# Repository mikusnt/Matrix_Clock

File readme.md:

# Matrix Clock
Documentation of electronic clock which matrix of LED's controlling by microcontroller ATmega 328P. Communication between clock and user realized by bluetooth. Room brightness determines matrix brightness.
# Processor
ATmega 328P 20MHz  
Period: 0,05 us = 50 ns  
Connected to:
* five shift registers to control the matrix (four to control X axes, one to control Y axis) 
* relay to generate acustic signals (quaters and full hours)
* DS3231 timer by I2C
* HC-06 bluetooth module by RS232
* photoresistor to brightness measurement

# Timers Math calculations

## Main timer (matrix refresh)
8bit Timer0  
Mode: CTC  
Refresh freq: 100 Hz  
Y levels of matrix: 8  
Number of brightness level: 20  
uC period of overflow: 20 000 000 / 100 / 8 / 20 =  1250  
Prescaler: 8  
OCR: 156  

## Logic PWM Timer (PWM matrix brightness)
16bit Timer1
Mode: CTC  
Refresh freq: 100 Hz  
Y levels of matrix: 8  
Number of brightness level: 20  
Number of PWM brightness levels: 3  
uC period of overflow: 20 000 000 / 100 / 8 / 20 / 3 =  417  
Prescaler: 8  
OCR: 52  

## Internal time timer (between DS3231 1Hz overflows)
8bit Timer2  
Mode: CTC  
Freq: 1kHz  
Period: 1ms  
uC period to overflow: 20 000 000 / 1 000 = 20 000  
Prescaler: 256    
OCR: 78  

## Power consumption
Basic mode: 20mA  
High brightness: 66mA  

Basic Mode + Bluetooth: 41mA  
High brightness + Bluetooth: 82mA

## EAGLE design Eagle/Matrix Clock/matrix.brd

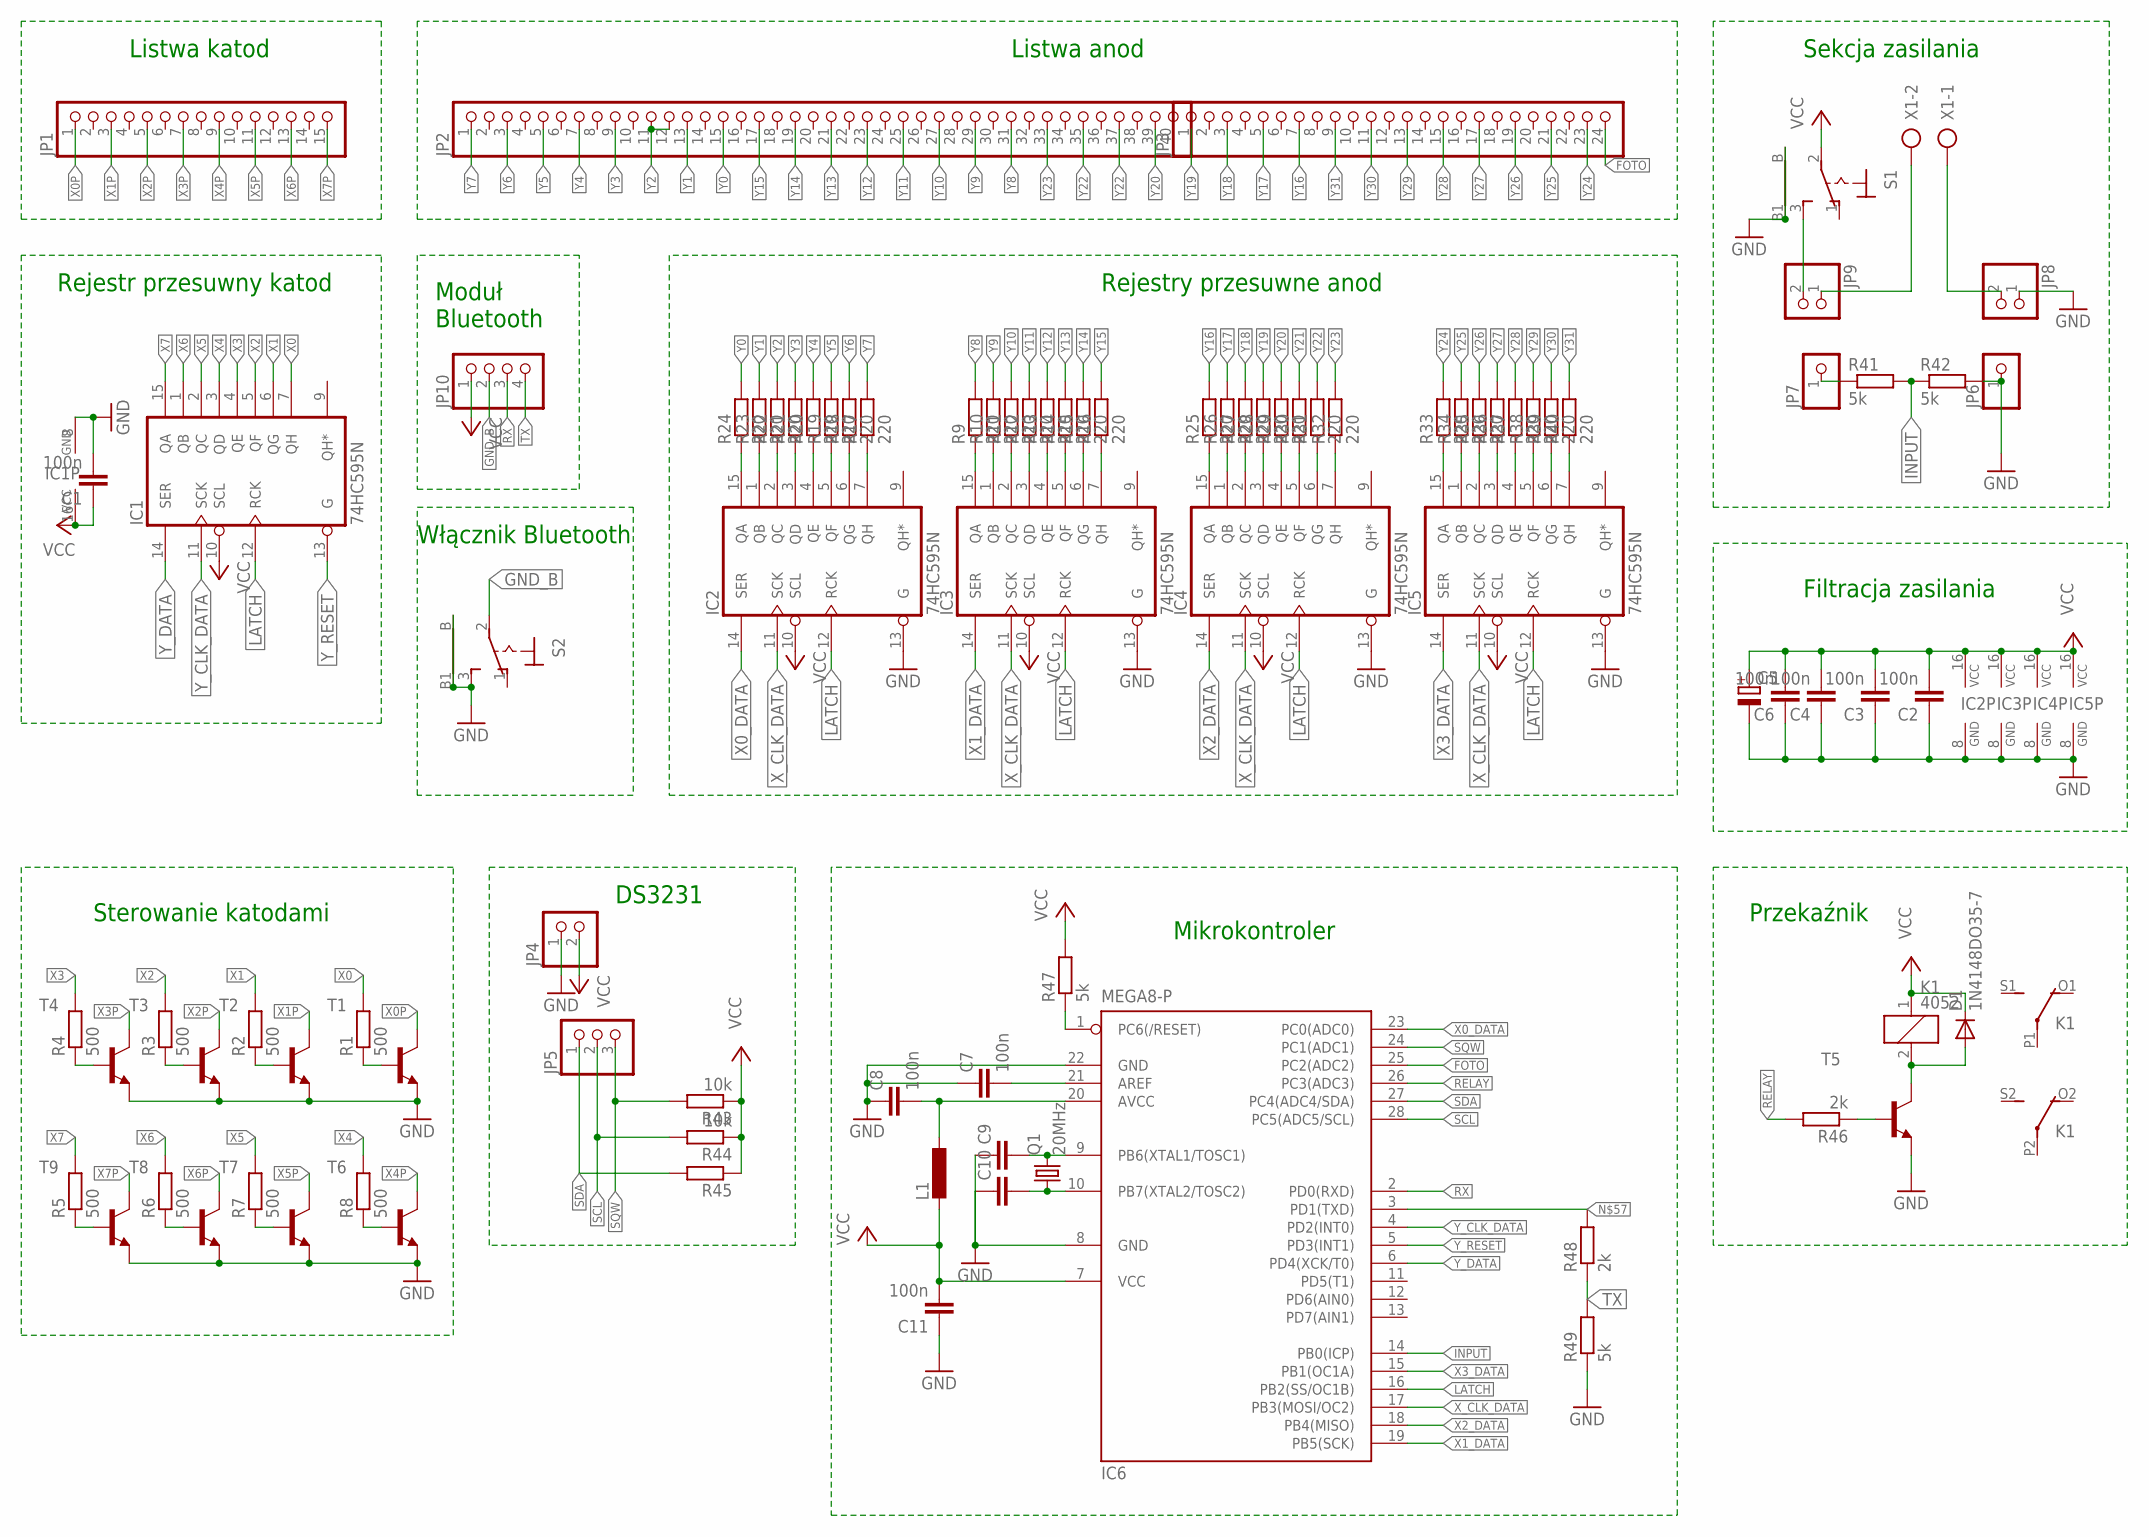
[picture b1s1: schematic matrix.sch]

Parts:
C1, C2, C3, C4, C6, C7, C8, C11: 100n; C025-025X050
C5: CPOL-EUE2.5-7; E2,5-7
C9, C10: C-EU025-025X050; C025-025X050
D1: 1N4148DO35-7; DO35-7
IC1, IC2, IC3, IC4, IC5: 74HC595N; DIL16
IC6: MEGA8-P; DIL28-3
JP1: PINHD-1X15; 1X15
JP2: PINHD-1X40; 1X40
JP3: PINHD-1X24; 1X24
JP4, JP8, JP9: PINHD-1X2; 1X02
JP5: PINHD-1X3; 1X03
JP6, JP7: PINHD-1X1; 1X01
JP10: PINHD-1X4; 1X04
K1: 4052; F4052
L1: L-EU0207/10; 0207/10
Q1: 20MHz; HC49/S
R1, R2, R3, R4, R5, R6, R7, R8: 500; 0204/5
R9, R10, R11, R12, R13, R14, R15, R16, R17, R20, R22, R23, R24, R25, R26, R27, R28, R29, R31, R32, R33, R34, R35, R37, R38, R39, R40: 220; 0204/5
R18, R19: 220; 0204V
R21, R30, R36, R45: R-EU_0204/5; 0204/5
R41, R42, R49: 5k; 0204/5
R43: 10k; 0207/7
R44: 10k; 0204/5
R46: 2k; 0207/7
R47: 5k; 0204V
R48: 2k; 0204/5
S1, S2: 9070-1W
T1, T2, T3, T4, T5, T6, T7, T8, T9: BC337-16-NPN-TO92-CBE; TO92-CBE
X1: AK300/2

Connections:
FOTO: IC6.25 (PC2(ADC2)), JP3.24
GND: C1.2, C2.1, C3.1, C4.1, C5.-, C6.1, C7.1, C8.1, C9.1, C10.1, C11.1, IC1.8 (GND), IC2.8 (GND), IC2.13 (G), IC3.8 (GND), IC3.13 (G), IC4.8 (GND), IC4.13 (G), IC5.8 (GND), IC5.13 (G), IC6.8 (GND), IC6.22 (GND), JP4.1, JP6.1, JP8.1, R42.2, R49.1, S1.B, S1.B1, S2.3 (S), S2.B, S2.B1, T1.E, T2.E, T3.E, T4.E, T5.E, T6.E, T7.E, T8.E, T9.E
GND_B: JP10.2, S2.2
INPUT: IC6.14 (PB0(ICP)), R41.2, R42.1
LATCH: IC1.12 (RCK), IC2.12 (RCK), IC3.12 (RCK), IC4.12 (RCK), IC5.12 (RCK), IC6.16 (PB2(SS/OC1B))
unnamed: R4.1, T4.B
unnamed: JP9.1, X1.2
unnamed: IC2.15 (QA), R24.1
unnamed: R3.1, T3.B
unnamed: R2.1, T2.B
unnamed: R1.1, T1.B
unnamed: R8.1, T6.B
unnamed: R7.1, T7.B
unnamed: R6.1, T8.B
unnamed: R5.1, T9.B
unnamed: JP8.2, X1.1
unnamed: IC2.1 (QB), R23.1
unnamed: IC2.2 (QC), R22.1
unnamed: JP7.1, R41.1
unnamed: IC2.3 (QD), R21.1
unnamed: IC2.4 (QE), R20.1
unnamed: IC2.5 (QF), R19.1
unnamed: IC2.6 (QG), R18.1
unnamed: IC2.7 (QH), R17.1
unnamed: IC3.15 (QA), R9.1
unnamed: IC3.1 (QB), R10.1
unnamed: IC3.2 (QC), R11.1
unnamed: IC3.3 (QD), R12.1
unnamed: IC3.4 (QE), R13.1
unnamed: IC3.5 (QF), R14.1
unnamed: IC3.6 (QG), R15.1
unnamed: IC3.7 (QH), R16.1
unnamed: IC4.7 (QH), R32.1
unnamed: IC4.6 (QG), R31.1
unnamed: IC4.5 (QF), R30.1
unnamed: IC4.4 (QE), R29.1
unnamed: IC4.3 (QD), R28.1
unnamed: IC4.2 (QC), R27.1
unnamed: IC4.1 (QB), R26.1
unnamed: IC4.15 (QA), R25.1
unnamed: JP9.2, S1.3 (S)
unnamed: C9.2, IC6.9 (PB6(XTAL1/TOSC1)), Q1.2
unnamed: C10.2, IC6.10 (PB7(XTAL2/TOSC2)), Q1.1
unnamed: C7.2, IC6.21 (AREF)
unnamed: IC5.15 (QA), R33.1
unnamed: IC5.1 (QB), R34.1
unnamed: IC5.2 (QC), R35.1
unnamed: IC5.3 (QD), R36.1
unnamed: IC5.4 (QE), R37.1
unnamed: IC5.5 (QF), R38.1
unnamed: IC5.6 (QG), R39.1
unnamed: IC5.7 (QH), R40.1
unnamed: C8.2, IC6.20 (AVCC), L1.1
unnamed: D1.A, K1.2, T5.C
unnamed: R46.1, T5.B
unnamed: IC6.1 (PC6(/RESET)), R47.1
unnamed: IC6.3 (PD1(TXD)), R48.2
RELAY: IC6.26 (PC3(ADC3)), R46.2
RX: IC6.2 (PD0(RXD)), JP10.3
SCL: IC6.28 (PC5(ADC5/SCL)), JP5.2, R44.2
SDA: IC6.27 (PC4(ADC4/SDA)), JP5.1, R45.2
SQW: IC6.24 (PC1(ADC1)), JP5.3, R43.2
TX: JP10.4, R48.1, R49.2
VCC: C1.1, C2.2, C3.2, C4.2, C5.+, C6.2, C11.2, D1.C, IC1.10 (SCL), IC1.16 (VCC), IC2.10 (SCL), IC2.16 (VCC), IC3.10 (SCL), IC3.16 (VCC), IC4.10 (SCL), IC4.16 (VCC), IC5.10 (SCL), IC5.16 (VCC), IC6.7 (VCC), JP4.2, JP10.1, K1.1, L1.2, R43.1, R44.1, R45.1, R47.2, S1.2
X0: IC1.7 (QH), R1.2
X0P: JP1.1, T1.C
X0_DATA: IC2.14 (SER), IC6.23 (PC0(ADC0))
X1: IC1.6 (QG), R2.2
X1P: JP1.3, T2.C
X1_DATA: IC3.14 (SER), IC6.19 (PB5(SCK))
X2: IC1.5 (QF), R3.2
X2P: JP1.5, T3.C
X2_DATA: IC4.14 (SER), IC6.18 (PB4(MISO))
X3: IC1.4 (QE), R4.2
X3P: JP1.7, T4.C
X3_DATA: IC5.14 (SER), IC6.15 (PB1(OC1A))
X4: IC1.3 (QD), R8.2
X4P: JP1.9, T6.C
X5: IC1.2 (QC), R7.2
X5P: JP1.11, T7.C
X6: IC1.1 (QB), R6.2
X6P: JP1.13, T8.C
X7: IC1.15 (QA), R5.2
X7P: JP1.15, T9.C
X_CLK_DATA: IC2.11 (SCK), IC3.11 (SCK), IC4.11 (SCK), IC5.11 (SCK), IC6.17 (PB3(MOSI/OC2))
Y0: JP2.15, R24.2
Y1: JP2.13, R23.2
Y2: JP2.11, JP2.12, R22.2
Y3: JP2.9, R21.2
Y4: JP2.7, R20.2
Y5: JP2.5, R19.2
Y6: JP2.3, R18.2
Y7: JP2.1, R17.2
Y8: JP2.31, R9.2
Y9: JP2.29, R10.2
Y10: JP2.27, R11.2
Y11: JP2.25, R12.2
Y12: JP2.23, R13.2
Y13: JP2.21, R14.2
Y14: JP2.19, R15.2
Y15: JP2.17, R16.2
Y16: JP3.7, R25.2
Y17: JP3.5, R26.2
Y18: JP3.3, R27.2
Y19: JP3.1, R28.2
Y20: JP2.39, R29.2
Y21: JP2.37, R30.2
Y22: JP2.35, R31.2
Y23: JP2.33, R32.2
Y24: JP3.23, R33.2
Y25: JP3.21, R34.2
Y26: JP3.19, R35.2
Y27: JP3.17, R36.2
Y28: JP3.15, R37.2
Y29: JP3.13, R38.2
Y30: JP3.11, R39.2
Y31: JP3.9, R40.2
Y_CLK_DATA: IC1.11 (SCK), IC6.4 (PD2(INT0))
Y_DATA: IC1.14 (SER), IC6.6 (PD4(XCK/T0))
Y_RESET: IC1.13 (G), IC6.5 (PD3(INT1))

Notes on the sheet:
DS3231
Przekaźnik
Włącznik Bluetooth
Sekcja zasilania
Listwa anod
Listwa katod
Filtracja zasilania
Rejestry przesuwne anod
Sterowanie katodami
Rejestr przesuwny katod
Moduł Bluetooth
Mikrokontroler

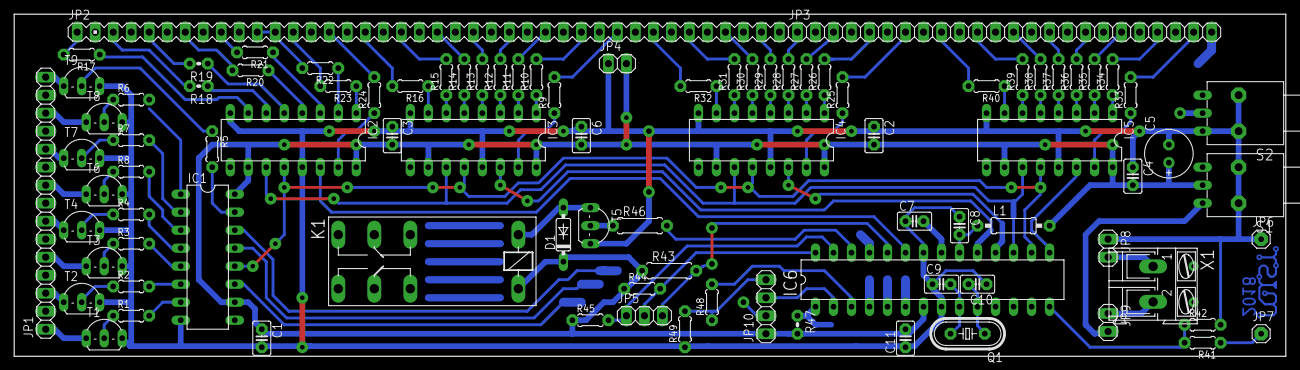
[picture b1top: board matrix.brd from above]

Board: 2 copper layers, 179.4 x 48.2 mm, 93 parts (1 on the bottom side), 120 nets.

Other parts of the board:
U$1: MIST

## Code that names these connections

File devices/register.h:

/*!
 * @file register.h
 * @author 		Mikolaj Stankowiak <br>
 * 				mik-stan@go2.pl
 * $Modified: 2018-10-31 $
 * $Created: 2017-11-04 $
 * @version 1.1
 *
 * Used uC pins: 9<br>
 * Header file containing 5 LED matrix shift registers. <br> <span class="rowny">
 * Model of register: serial in (1 bit), parallel out(8 bit) 74HC595
 * ___|X0_____________________|X1____________________|X2_____________________|X3____________________		<br>
 * ___|0__1__2__3__4__5__6__7_|0__1__2__3__4__5__6__7|0__1__2__3__4__5__6__7_|0__1__2__3__4__5__6__7		<br>
 * ____0__1__2__3__4__5__6__7__8__9_10_11_12_13_14_15_16_17_18_19_20_21_22_23_24_25_26_27_28_29_30_31		<br>
 * Y_0|																										<br>
 * __1|																										<br>
 * __2|																										<br>
 * __3|																										<br>
 * __4|																										<br>
 * __5|																										<br>
 * __6|																										<br>
 * __7|																										<br>
 * </span>																											<br>
 * Features:<br>
 * 		- different serial data input to all register <br>
 * 		- same serial clock signal ro X register, different to Y <br>
 * 		- wspolny sygnal zegarowy dla zatrzasku wyjscia rownoneglego dla rejestrow X i Y<br>
 * 		- same parallel data
 * 		- rejestr Y posiada sterowanie stanem wyjscia rownoleglego, mozna przejsc na stan wysokiej
 * 	      impedancji, co jest wykorzystywane w wylaczeniu calej matrycy, niestety efekt duchow<br>
 * 	      nalezalo obejsc poprzez zaladowanie zer dla X0-X4, dopiero pozniej mozna przelaczyc Y
 *
 * @see DiodeMatrix
 */

#ifndef register_H_
#define register_H_

#include "../group_includes.h"

/*
 *
 *		IO macros
 *
 */


/*
 *		X0
 */
//! direction register of serial data input X0
#define X0_DATA_DDR DDRC
//! state register of serial data input X0
#define X0_DATA_PORT PORTC
//! address of serial data input X0
#define X0_DATA_ADDR (1 << PC0)
//! set high state to serial data input X0
#define X0_DATA_HIGH() X0_DATA_PORT |= X0_DATA_ADDR
//! set low state to serial data input X0
#define X0_DATA_LOW() X0_DATA_PORT &= ~X0_DATA_ADDR


/*
 *		X1
 */
//! direction register of serial data input X1
#define X1_DATA_DDR DDRB
//! state register of serial data input X1
#define X1_DATA_PORT PORTB
//! address of serial data input X1
#define X1_DATA_ADDR (1 << PB5)
//! set high state to serial data input X1
#define X1_DATA_HIGH() X1_DATA_PORT |= X1_DATA_ADDR
//! set low state to serial data input X1
#define X1_DATA_LOW() X1_DATA_PORT &= ~X1_DATA_ADDR


/*
 * 		X2
 */
//! direction register of serial data input X2
#define X2_DATA_DDR DDRB
//! state register of serial data input X2
#define X2_DATA_PORT PORTB
//! address of serial data input X2
#define X2_DATA_ADDR (1 << PB4)
//! set high state to serial data input X2
#define X2_DATA_HIGH() X2_DATA_PORT |= X2_DATA_ADDR
//! set low state to serial data input X2
#define X2_DATA_LOW() X2_DATA_PORT &= ~X2_DATA_ADDR

/*
 *		X3
 */
//! direction register of serial data input X3
#define X3_DATA_DDR DDRB
//! state register of serial data input X3
#define X3_DATA_PORT PORTB
//! address of serial data input X3
#define X3_DATA_ADDR (1 << PB1)
//! set high state to serial data input X3
#define X3_DATA_HIGH() X3_DATA_PORT |= X3_DATA_ADDR
//! set low state to serial data input X3
#define X3_DATA_LOW() X3_DATA_PORT &= ~X3_DATA_ADDR

/*
 *		Y
 */
//! direction register of serial data input Y
#define Y_DATA_DDR DDRD
//! state register of serial data input Y
#define Y_DATA_PORT PORTD
//! address of serial data input Y
#define Y_DATA_ADDR (1 << PD4)
//! set high state to serial data input Y
#define Y_DATA_HIGH() Y_DATA_PORT |= Y_DATA_ADDR
//! set low state to serial data input Y
#define Y_DATA_LOW() Y_DATA_PORT &= ~Y_DATA_ADDR

/*
 *		X_CLK_DATA
 */
//! direction register of clk of X group serial data inputs
#define X_CLK_DATA_DDR DDRB
//! state register of clk of X group serial data inputs
#define X_CLK_DATA_PORT PORTB
//! address of clk of X group serial data inputs
#define X_CLK_DATA_ADDR (1 << PB3)


/*
 *		Y_CLK_DATA
 */
//! direction register of clk of Y serial data input Y
#define Y_CLK_DATA_DDR DDRD
//! state register of clk of Y serial data input
#define Y_CLK_DATA_PORT PORTD
//! state register of clk of Y serial data input
#define Y_CLK_DATA_ADDR (1 << PD2)


/*
 *		Y_RESET, not used
 */
//! direction register of reset Y register
#define Y_RESET_DDR DDRD
//! state register of reset Y register
#define Y_RESET_PORT PORTD
//! address of reset Y register
#define Y_RESET_ADDR (1 << PD3)
//! set ON Y register
#define Y_ON() Y_RESET_PORT &= ~Y_RESET_ADDR
//! set OFF Y register
#define Y_OFF() Y_RESET_PORT |= Y_RESET_ADDR

/*
 *		LATCH
 */
//! direction register of parallel output enable of all registers
#define LATCH_DDR DDRB
//! state register of parallel output enable of all registers
#define LATCH_PORT PORTB
//! address of parallel output enable of all registers
#define LATCH_ADDR (1 << PB2)
//! set high state of parallel output enable of all registers
#define LATCH_HIGH() LATCH_PORT |= LATCH_ADDR
//! set low state of parallel output enable of all registers
#define LATCH_LOW() LATCH_PORT &= ~LATCH_ADDR


/*
 *
 *		Declaration of functions
 *
 */
//! initialize registers
extern void RegistersInit();
//! send one bit to Y register
inline void SendRegisterY(volatile BinarySwitch eB, bool bWithLoad);
//! send byte table to X0 - X3 registers
inline void SendRegistersX(volatile uint8_t uitLineBuffer[32], bool bWithLoad);
//! send zeros to X0 - X3 registers
inline void ClearRegistersX(bool bWithLoad);
//! send byte table only to X0 register
inline void SendRegisterX(volatile uint8_t uitBuffer[8], bool bWithLoad);

/*
 *
 * 		Definitions of inline functions
 *
 */

//! to load new byte to Y register
inline void Y_CLK_01() {
	Y_CLK_DATA_PORT &= ~Y_CLK_DATA_ADDR;
	Y_CLK_DATA_PORT |= Y_CLK_DATA_ADDR;
}

//! to load new bytes to X registers
inline void X_CLK_01() {
	X_CLK_DATA_PORT &= ~X_CLK_DATA_ADDR;
	X_CLK_DATA_PORT |= X_CLK_DATA_ADDR;

}

//! to reload parallel output in all registers
inline void LATCH_01() {
	LATCH_LOW();
	LATCH_HIGH();
}

/*! @param		eB new logic value
 *  @param		bWithLoad enable to reload parallel output*/
inline void SendRegisterY(volatile BinarySwitch eB, bool bWithLoad) {
	if (eB)
		Y_DATA_HIGH();
	else
		Y_DATA_LOW();
	Y_CLK_01();
	if (bWithLoad) LATCH_01();
} // END inline void SendRegisterY

/*! @param		uitLineBuffer logic bytes of registers state
 *  @param		bWithLoad enable to reload parallel output*/
inline void SendRegistersX(volatile uint8_t uitLineBuffer[32], bool bWithLoad) {
	register int8_t i; // required fast operations

	for (i = 0; i < 8; i++) {
		if (uitLineBuffer[0 + i]) X0_DATA_HIGH();
			else X0_DATA_LOW();
		if (uitLineBuffer[8 + i]) X1_DATA_HIGH();
			else X1_DATA_LOW();
		if (uitLineBuffer[16 + i]) X2_DATA_HIGH();
			else X2_DATA_LOW();
		if (uitLineBuffer[24 + i]) X3_DATA_HIGH();
			else X3_DATA_LOW();
		X_CLK_01();
	}
	if (bWithLoad) LATCH_01();
} // END inline void SendRegistersX

/*! @param		bWithLoad enable to reload parallel output*/
inline void ClearRegistersX(bool bWithLoad) {
	register uint8_t i;
	X0_DATA_LOW();
	X1_DATA_LOW();
	X2_DATA_LOW();
	X3_DATA_LOW();
	for (i = 0; i < 8; i++) {
		X_CLK_01();
	}
	if (bWithLoad) LATCH_01();
} // END inline void SendRegistersX

/*!  @param		uitBuffer logic bytes of X0 state
 *   @param		bWithLoad enable to reload parallel output*/
inline void SendRegisterX(volatile uint8_t uitBuffer[8], bool bWithLoad) {
	register int8_t i;
	for (i = 0; i < 8; i++) {
		if (uitBuffer[i]) X0_DATA_HIGH();
			else X0_DATA_LOW();
		X_CLK_01();
	}
	if (bWithLoad) LATCH_01();
} // END inline void SendRegisterX

#endif /* 54HC595_H_ */

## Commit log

2017-12-02 inicjalizacja projektu
2017-12-02 usus
2017-12-02 Revert "usus"
    This reverts commit 61b22355cfab14de84cc42d04e5c7a4532abb941.
2017-12-02 poprawka
2017-12-02 with no release
2017-12-02 bez plikow
2017-12-02 inicjalizacja
2017-12-02 poprawki ADC
2017-12-02 drobne zmiany relay.h
2017-12-16 poprawki relay, bluetooth od MK
2017-12-16 dodanie Eagle
2017-12-17 korekta gitignore
2017-12-23 rozszerzenie UART
    dokumentacja mkuart, szkielet przetwarzania polecen z uart
2017-12-27 poprawki komentarzy
2018-03-25 zmiany pinout
2018-03-28 uruchomienie wyswietlania czasu
2018-03-29 dokumentacja, jasnosc po ADC
2018-03-31 optymalizacja, UART
2018-04-01 normalizacja komend UART
2018-04-02 piksel jako bit
2018-04-02 dokumentacja, optymalizacja
2018-04-04 dostosowanie parametrow
2018-04-12 naprawa bledow UART
2018-04-12 on, off przekaznika; powiekszone bufory
2018-04-13 added html documentation
2018-04-13 translate to english part 1
2018-04-13 repair readme
2018-04-15 translate main to english
2018-04-18 text debug mode
2018-04-29 translate to english seq folder
2018-05-05 devices state function
2018-05-05 Revert "devices state function"
    This reverts commit 6992d3211c2244062091a277c1d61c8e68458d42.
2018-05-05 Revert "Revert "devices state function""
    This reverts commit 4021bc0a6d3afba2798bdab1a76d974e5dab8144.
2018-05-05 translate to english data_types folder
2018-05-05 rename readme
2018-05-11 Auto stash before merge of "master" and "origin/master"
2018-05-11 translate bluetooth
2018-05-11 translate relay
2018-05-11 translate register
2018-05-11 translate some_devices
2018-05-11 final translate
2018-05-11 PixBit v0.94
2018-05-11 new tasks
2018-05-11 repair todo list
2018-05-11 relay clicking functions
2018-05-11 bomb clicking
2018-05-13 bomb seq
2018-05-14 repair version code
2018-05-16 create alpgabet generator jva project
2018-05-16 Revert "create alpgabet generator jva project"
    This reverts commit 957c881263f2050e14b2cc2f85b28a6659dbe688.
2018-05-16 create alphabet generator project in java
2018-05-16 Revert "bomb seq"
    This reverts commit 890cb8a353cb1b220ff8ba11ac56c824da90de0c.
2018-05-16 Revert "Auto stash before merge of "master" and "origin/master""
    This reverts commit f7b860d9439c9917c96ccb98801d93677a663e19.
2018-05-16 Revert "Revert "Auto stash before merge of "master" and "origin/master"""
    This reverts commit ee04c1e6be12e5b0c4a3d7b9170414f2543267f3.
2018-05-16 corrent reverts commits
2018-05-17 swing window operations
2018-05-17 rename gitignore
2018-05-17 char length
2018-05-17 table reactions
2018-05-18 cut Alphabet_Generator to another project
2018-05-18 separate alphabet and alphabet codes
2018-05-18 rename alphabet and alphabet_codes header structure
2018-10-10 relay time modifications, dots progress to long decrement counter
2018-10-11 add long decounter sequence without save data to eeprom
2018-10-15 write and read date to eeprom, relay parameters
2018-10-15 optimisation, cosmetic changes
2018-10-16 texts to eeprom
2018-10-20 displaying all texts from eeprom
2018-10-20 untested migration to full ASCII Alphabet from Alphabet Generator
2018-10-20 two relay work modes
2018-10-20 doxygen repair by change PROGMEM directive location
2018-10-21 alphabet, gamma corrections
2018-10-21 hardware brightness of matrix, english comments
2018-10-21 reverse hardware brightness, ghost effect on matrix
2018-10-28 hardware brightness as second brightness regulation, untested
2018-10-28 cosmetic changes
2018-10-28 critical section of matrix refresh
2018-10-29 critical section test, deactivate pwm matrix brightness
2018-10-31 version 1.1
2019-01-03 repair bug of full bluetooth buffer, untested
2019-01-04 version 1.11
2019-01-07 Pixels position of seconds and parameters, : design
2019-01-07 doxyfiles
2019-01-16 spectrum analyzer frame, untested
